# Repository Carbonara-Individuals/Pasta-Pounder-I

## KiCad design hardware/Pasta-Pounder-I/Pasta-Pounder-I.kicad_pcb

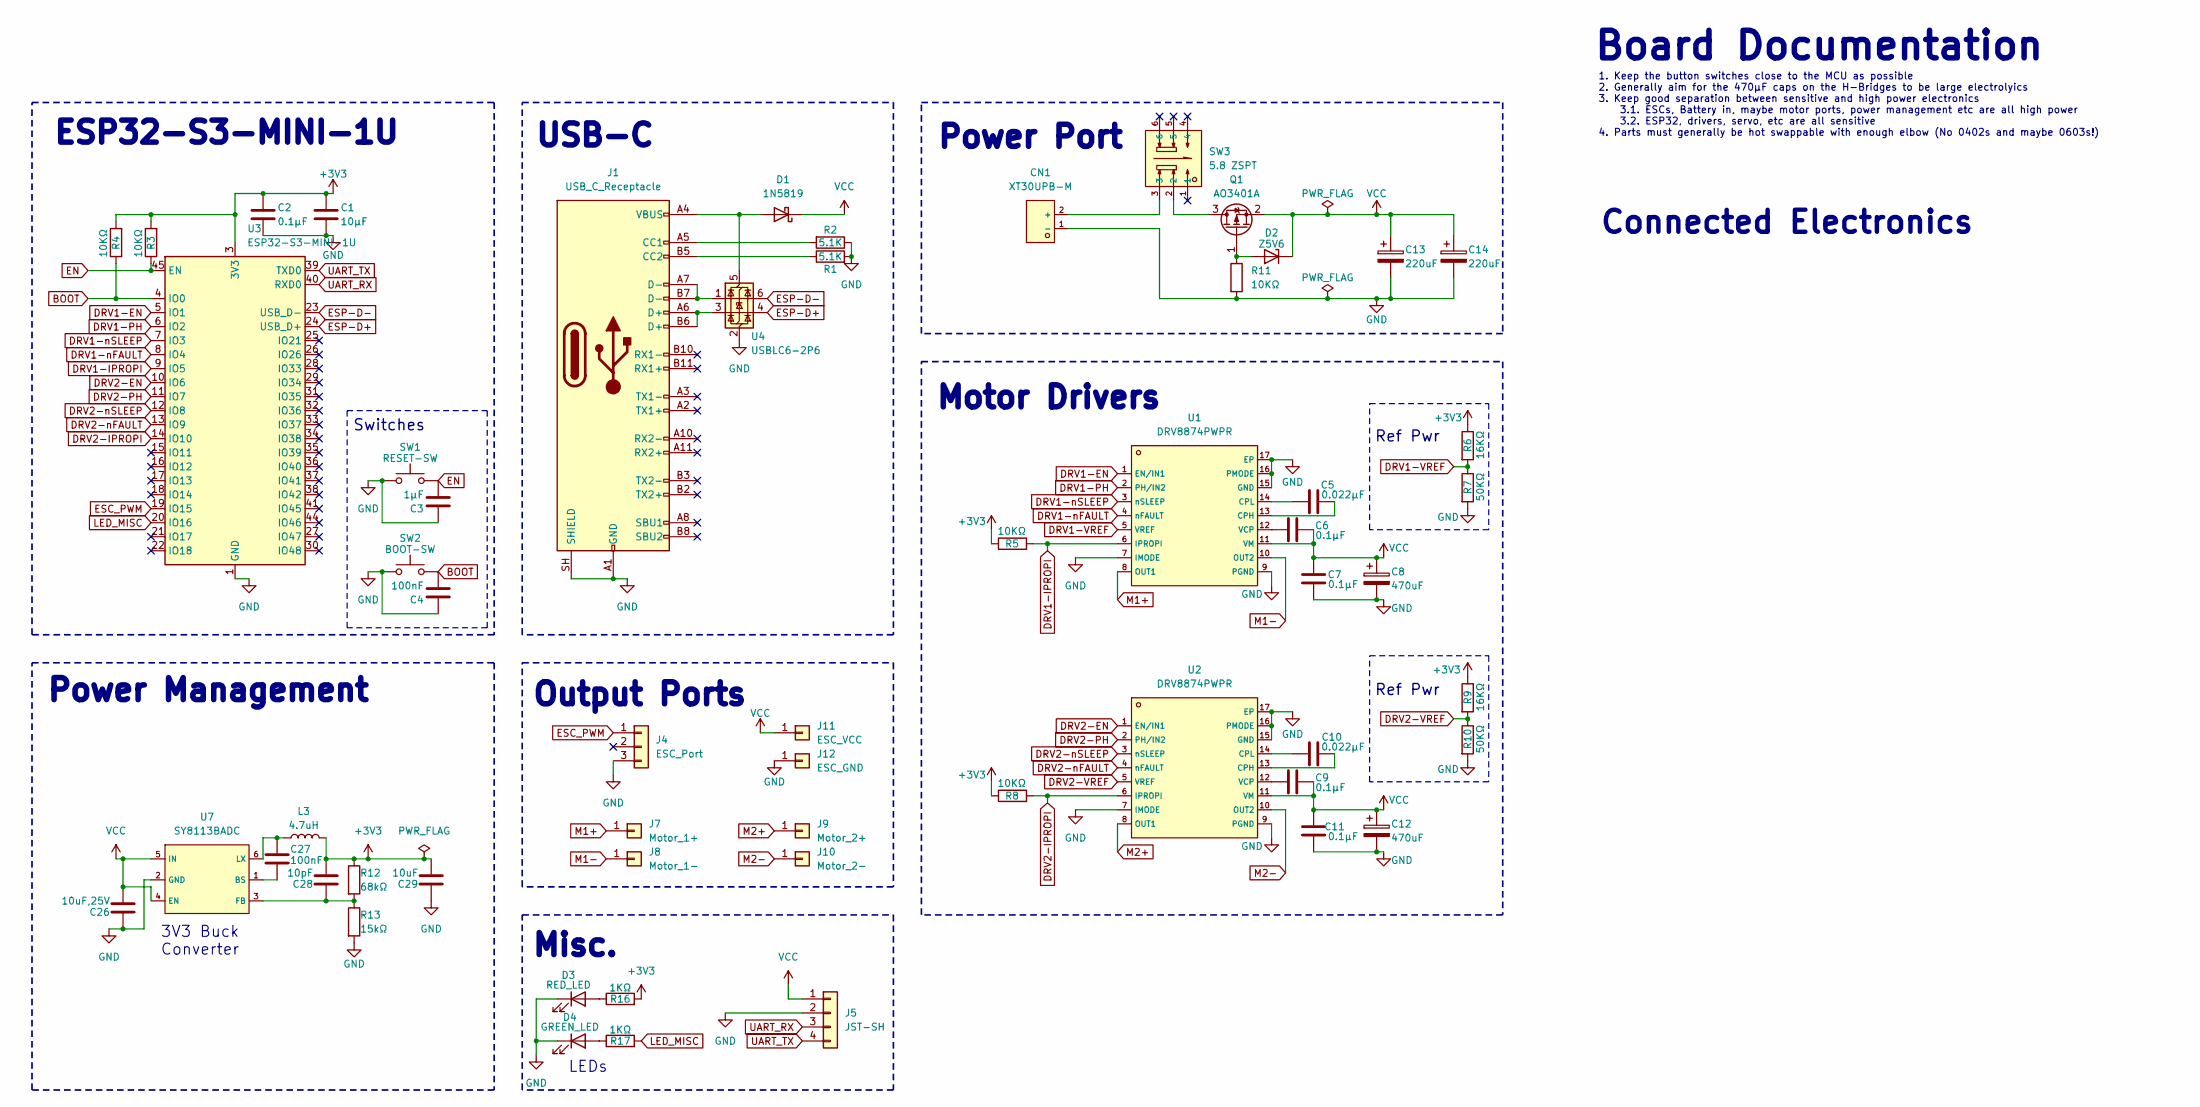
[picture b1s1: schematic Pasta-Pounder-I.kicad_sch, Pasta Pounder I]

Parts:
C1: 10µF; C_0603
C2, C6, C7, C9, C11: 0.1µF; C_0603
C3: 1µF; C_0603
C4: 100nF; C_0603
C5, C10: 0.022µF; C_0603
C8, C12: 470uF; C_0805
C13, C14: 220uF; CP_Elec_6.3x7.7
C26: 10uF,25V; C_0603
C27: 100nF; C_0402
C28: 10pF; C_0402
C29: 10uF; C_0603
CN1: XT30UPB-M; C428721_CONN-TH_XT30UPB-M; LCSC C428721
D1: 1N5819; D_SOD-323
D2: Z5V6; D_SOD-123; Part MM1Z5V6; LCSC C22395539
D3: RED_LED; D_0603
D4: GREEN_LED; D_0603
J1: USB_C_Receptacle; C165948_USB-C_SMD-TYPE-C-31-M-12_1
J4: ESC_Port; PinHeader_1x03_P2.54mm_Vertical
J5: JST-SH; JST_SH_BM04B-SRSS-TB_1x04-1MP_P1.00mm_Vertical
J7: Motor_1+; SolderWirePad_1x01_SMD_2x4mm
J8: Motor_1-; SolderWirePad_1x01_SMD_2x4mm
J9: Motor_2+; SolderWirePad_1x01_SMD_2x4mm
J10: Motor_2-; SolderWirePad_1x01_SMD_2x4mm
J11: ESC_VCC; SolderWirePad_1x01_SMD_2x4mm
J12: ESC_GND; SolderWirePad_1x01_SMD_2x4mm
L3: 4.7uH; C98354_IND-SMD_L2_5-W2_0_WPN252012H
Q1: AO3401A; Q_SOT-23
R1, R2: 5.1K; R_0603
R3, R4, R5, R8, R11: 10KΩ; R_0603
R6, R9: 16KΩ; R_0603
R7, R10: 50KΩ; R_0603
R12: 68kΩ; R_0603
R13: 15kΩ; R_0603
R16, R17: 1KΩ; R_0603
SW1: RESET-SW; C115357_SW-SMD_L3_9-W3_0-P4_45
SW2: BOOT-SW; C115357_SW-SMD_L3_9-W3_0-P4_45
SW3: 5.8 ZSPT; C2681588_SW-TH_5_8ZSPT; LCSC C2681588
U1, U2: DRV8874PWPR; C1855818_HTSSOP-16_L5_0-W4_4-P0_65-LS6_4-BL-EP; LCSC C1855818
U3: ESP32-S3-MINI-1U; ESP32-S2-MINI-1U
U4: USBLC6-2P6; SOT-666
U7: SY8113BADC; C78989_TSOT-23-6_L2_9-W1_6-P0_95-LS2_8-BR; LCSC C78989

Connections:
+3V3: C1.1, C2.1, C28.2, C29.2, L3.2, R3.2, R4.2, R5.1, R6.1, R8.1, R9.1, R12.1, R16.2, U3.3 (3V3)
BOOT: C4.2, R4.1, SW2.2, U3.4 (IO0)
DRV1-EN: U1.1 (EN/IN1), U3.5 (IO1)
DRV1-IPROPI: R5.2, U1.6 (IPROPI), U3.9 (IO5)
DRV1-PH: U1.2 (PH/IN2), U3.6 (IO2)
DRV1-VREF: R6.2, R7.1, U1.5 (VREF)
DRV1-nFAULT: U1.4 (nFAULT), U3.8 (IO4)
DRV1-nSLEEP: U1.3 (nSLEEP), U3.7 (IO3)
DRV2-EN: U2.1 (EN/IN1), U3.10 (IO6)
DRV2-IPROPI: R8.2, U2.6 (IPROPI), U3.14 (IO10)
DRV2-PH: U2.2 (PH/IN2), U3.11 (IO7)
DRV2-VREF: R9.2, R10.1, U2.5 (VREF)
DRV2-nFAULT: U2.4 (nFAULT), U3.13 (IO9)
DRV2-nSLEEP: U2.3 (nSLEEP), U3.12 (IO8)
EN: C3.2, R3.1, SW1.2, U3.45 (EN)
ESC_PWM: J4.1, U3.19 (IO15)
ESP-D+: U3.24 (USB_D+), U4.4 (I/O2)
ESP-D-: U3.23 (USB_D-), U4.6 (I/O1)
GND: C1.2, C2.2, C3.1, C4.1, C7.1, C8.2, C11.1, C12.2, C13.2, C14.2, C26.1, C29.1, CN1.1 (-), D3.1 (K), D4.1 (K), J1.A1 (GND), J1.A12 (GND), J1.B1 (GND), J1.B12 (GND), J1.SH (SHIELD), J4.3, J5.2, J12.1 (Pin_1_1), R1.2, R2.1, R7.2, R10.2, R11.2, R13.2, SW1.1, SW2.1, U1.7 (IMODE), U1.9 (PGND), U1.15 (GND), U1.16 (PMODE), U1.17 (EP), U2.7 (IMODE), U2.9 (PGND), U2.15 (GND), U2.16 (PMODE), U2.17 (EP), U3.1 (GND), U3.2 (GND), U3.42 (GND), U3.43 (GND), U3.46 (GND), U3.47 (GND), U3.48 (GND), U3.49 (GND), U3.50 (GND), U3.51 (GND), U3.52 (GND), U3.53 (GND), U3.54 (GND), U3.55 (GND), U3.56 (GND), U3.57 (GND), U3.58 (GND), U3.59 (GND), U3.60 (GND), U3.61 (GND), U3.62 (GND), U3.63 (GND), U3.64 (GND), U3.65 (GND), U4.2 (GND), U7.2 (GND)
LED_MISC: R17.2, U3.20 (IO16)
M1+: J7.1 (Pin_1_1), U1.8 (OUT1)
M1-: J8.1 (Pin_1_1), U1.10 (OUT2)
M2+: J9.1 (Pin_1_1), U2.8 (OUT1)
M2-: J10.1 (Pin_1_1), U2.10 (OUT2)
unnamed: CN1.2 (+), SW3.3
unnamed: D1.2 (A), J1.A4 (VBUS), J1.A9 (VBUS), J1.B4 (VBUS), J1.B9 (VBUS), U4.5 (VBUS)
unnamed: D3.2 (A), R16.1
unnamed: D4.2 (A), R17.1
unnamed: J1.A5 (CC1), R2.2
unnamed: J1.B5 (CC2), R1.1
unnamed: J1.A6 (D+), J1.B6 (D+), U4.3 (I/O2)
unnamed: J1.A7 (D-), J1.B7 (D-), U4.1 (I/O1)
unnamed: Q1.3 (D), SW3.2
unnamed: D2.2, Q1.1 (G), R11.1
unnamed: C5.2, U1.13 (CPH)
unnamed: C5.1, U1.14 (CPL)
unnamed: C6.1, U1.12 (VCP)
unnamed: C10.2, U2.13 (CPH)
unnamed: C10.1, U2.14 (CPL)
unnamed: C9.1, U2.12 (VCP)
unnamed: C27.1, U7.1 (BS)
unnamed: C28.1, R12.2, R13.1, U7.3 (FB)
unnamed: C27.2, L3.1, U7.6 (LX)
UART_RX: J5.3, U3.40 (RXD0)
UART_TX: J5.4, U3.39 (TXD0)
VCC: C6.2, C7.2, C8.1, C9.2, C11.2, C12.1, C13.1, C14.1, C26.2, D1.1 (K), D2.1, J5.1, J11.1 (Pin_1_1), Q1.2 (S), U1.11 (VM), U2.11 (VM), U7.4 (EN), U7.5 (IN)

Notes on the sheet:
Ref Pwr
Switches
Power Management
Board Documentation
Misc.
Output Ports
3V3 Buck Converter
Motor Drivers
Power Port
1. Keep the button switches close to the MCU as possible 2. Generally aim for the 470µF caps on the H-Bridges to be large electrolyics 3. Keep good separation between sensitive and high power electronics 3.1. ESCs, Battery in, maybe motor ports, power management etc are all high power 3.2. ESP32, d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
ESP32-S3-MINI-1U
Connected Electronics
LEDs
USB-C

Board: 4 copper layers, 57 parts (0 on the bottom side), 46 nets, no tracks yet.
